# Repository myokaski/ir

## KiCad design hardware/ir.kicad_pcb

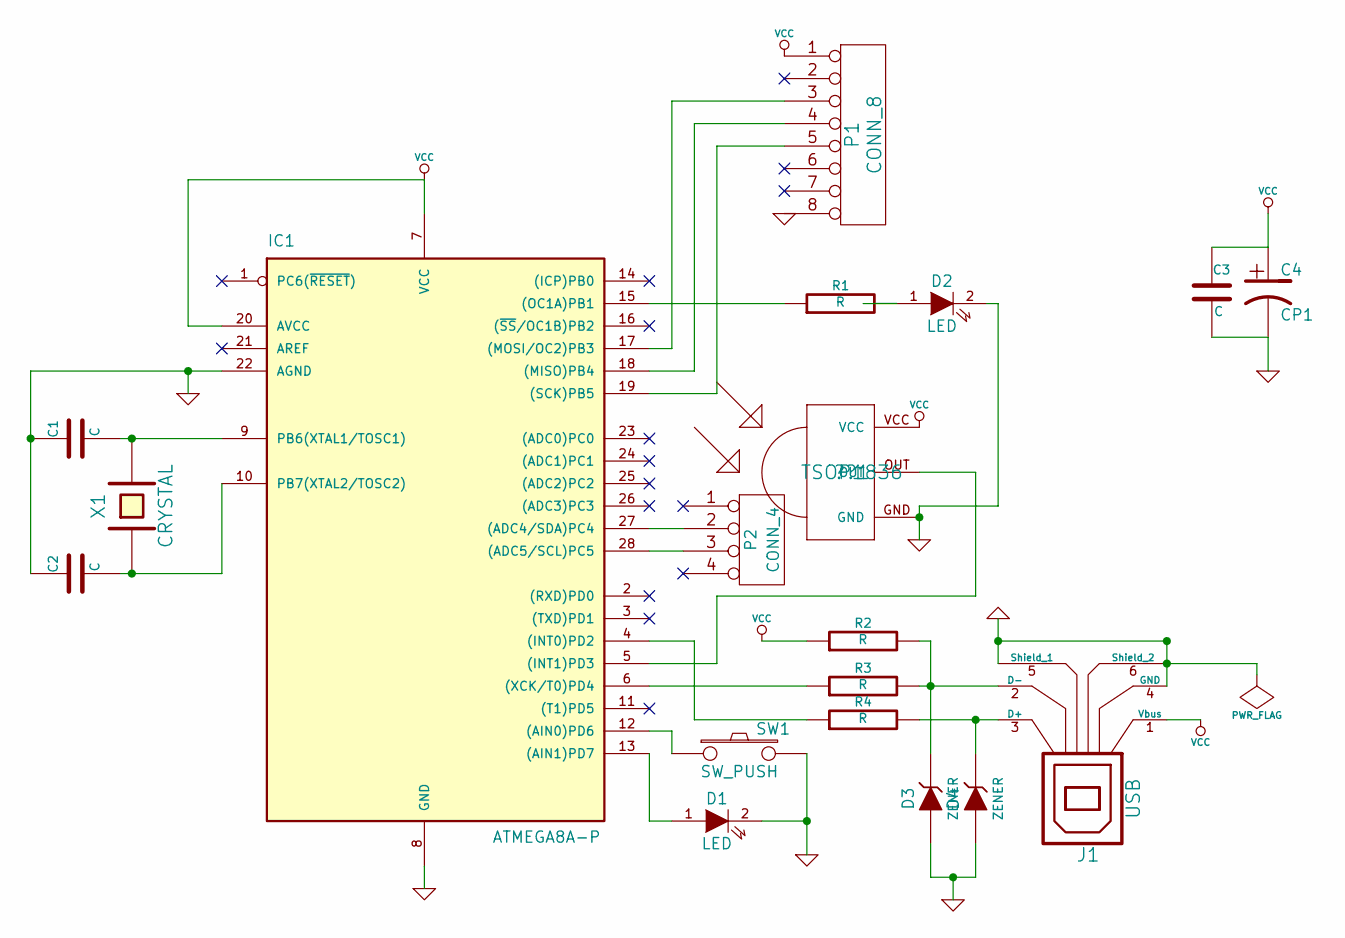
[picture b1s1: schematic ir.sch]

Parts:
??1: TSOP1836
C1, C2, C3: C
C4: CP1
D1, D2: LED
D3, D4: ZENER
IC1: ATMEGA8A-P; DIL28
J1: USB
P1: CONN_8
P2: CONN_4
R1, R2, R3, R4: R
SW1: SW_PUSH
X1: CRYSTAL

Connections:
GND: ??1.GND, C1.1, C2.1, C3.2, C4.2, D1.2 (K), D2.2 (K), D3.1 (A), D4.1 (A), IC1.8 (GND), IC1.22 (AGND), J1.4 (GND), J1.5 (Shield_1), J1.6 (Shield_2), P1.8, SW1.2
unnamed: IC1.19 ((SCK)PB5), P1.5
unnamed: ??1.OUT, IC1.5 ((INT1)PD3)
unnamed: IC1.15 ((OC1A)PB1), R1.1
unnamed: D2.1 (A), R1.2
unnamed: IC1.17 ((MOSI/OC2)PB3), P1.3
unnamed: IC1.18 ((MISO)PB4), P1.4
unnamed: IC1.12 ((AIN0)PD6), SW1.1
unnamed: D1.1 (A), IC1.13 ((AIN1)PD7)
unnamed: IC1.27 ((ADC4/SDA)PC4), P2.2
unnamed: IC1.28 ((ADC5/SCL)PC5), P2.3
unnamed: IC1.6 ((XCK/T0)PD4), R3.1
unnamed: IC1.4 ((INT0)PD2), R4.1
unnamed: D4.2 (K), J1.3 (D+), R4.2
unnamed: D3.2 (K), J1.2 (D-), R2.2, R3.2
unnamed: C1.2, IC1.9 (PB6(XTAL1/TOSC1)), X1.2
unnamed: C2.2, IC1.10 (PB7(XTAL2/TOSC2)), X1.1
VCC: ??1.VCC, C3.1, C4.1, IC1.7 (VCC), IC1.20 (AVCC), J1.1 (Vbus), P1.1, R2.1

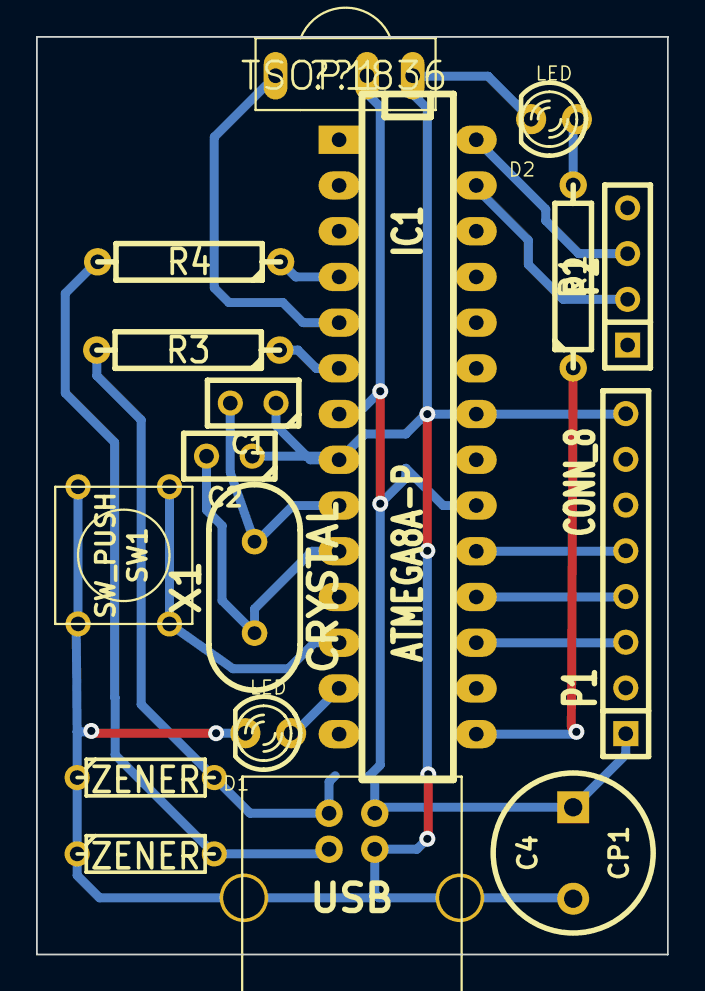
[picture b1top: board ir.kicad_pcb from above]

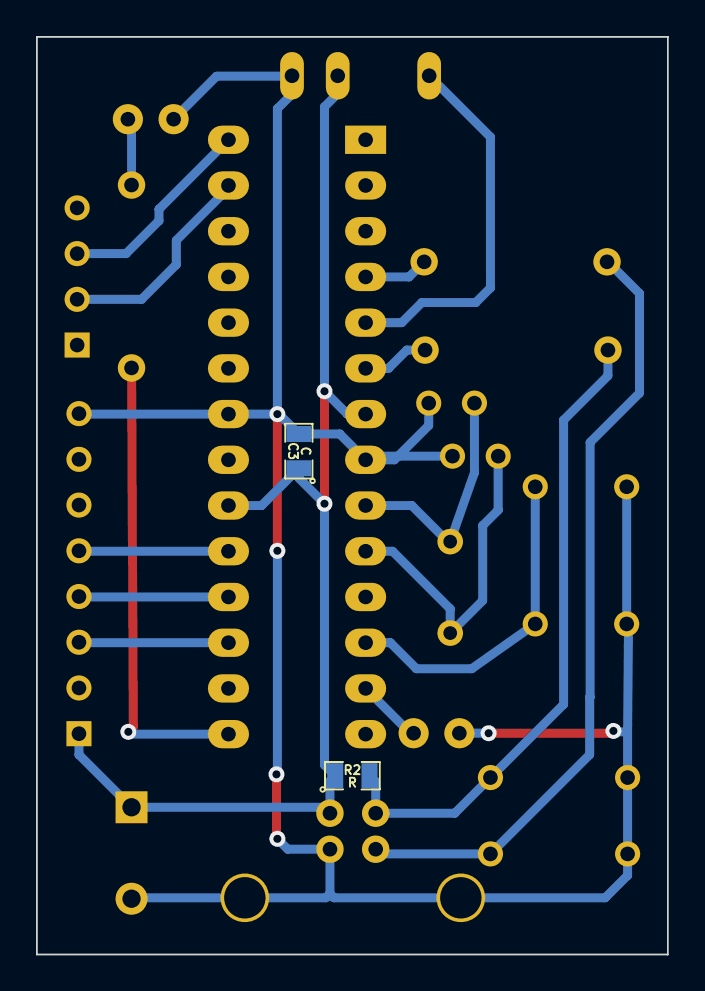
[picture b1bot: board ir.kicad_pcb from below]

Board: 2 copper layers, 35.1 x 51.0 mm, 19 parts (2 on the bottom side), 18 nets.

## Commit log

2017-02-21 Add hw files
2017-02-27 Remove some unuserd code
